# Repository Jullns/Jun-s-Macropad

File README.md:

# Macropad ✨
This is my macropad for music design and art. Following the tutorial from the blueprint program but adding some changes.

-----
## BOM:
- Seeed XIAO RP2040
- EC11 Rotary encoder
- MX-Style switches (x8)
- Blank DSA keycaps (x8)
- SK6812 MINI-E LEDs (x2)
- 4x M3x16 Bolt
- 4x M3 Heatset

## Screenshots:
- Schematic:

- PCB:

- Case:

## Challenges:

In this project, I learned a lot about using KiCad and Fusion, finally bringing the Macropad project to life. My biggest challenge was Fusion, as I had never used 3D design software before. I had to follow many steps to create the case; however, by following tutorials and doing research, I successfully completed the project and gained a great deal of knowledge.

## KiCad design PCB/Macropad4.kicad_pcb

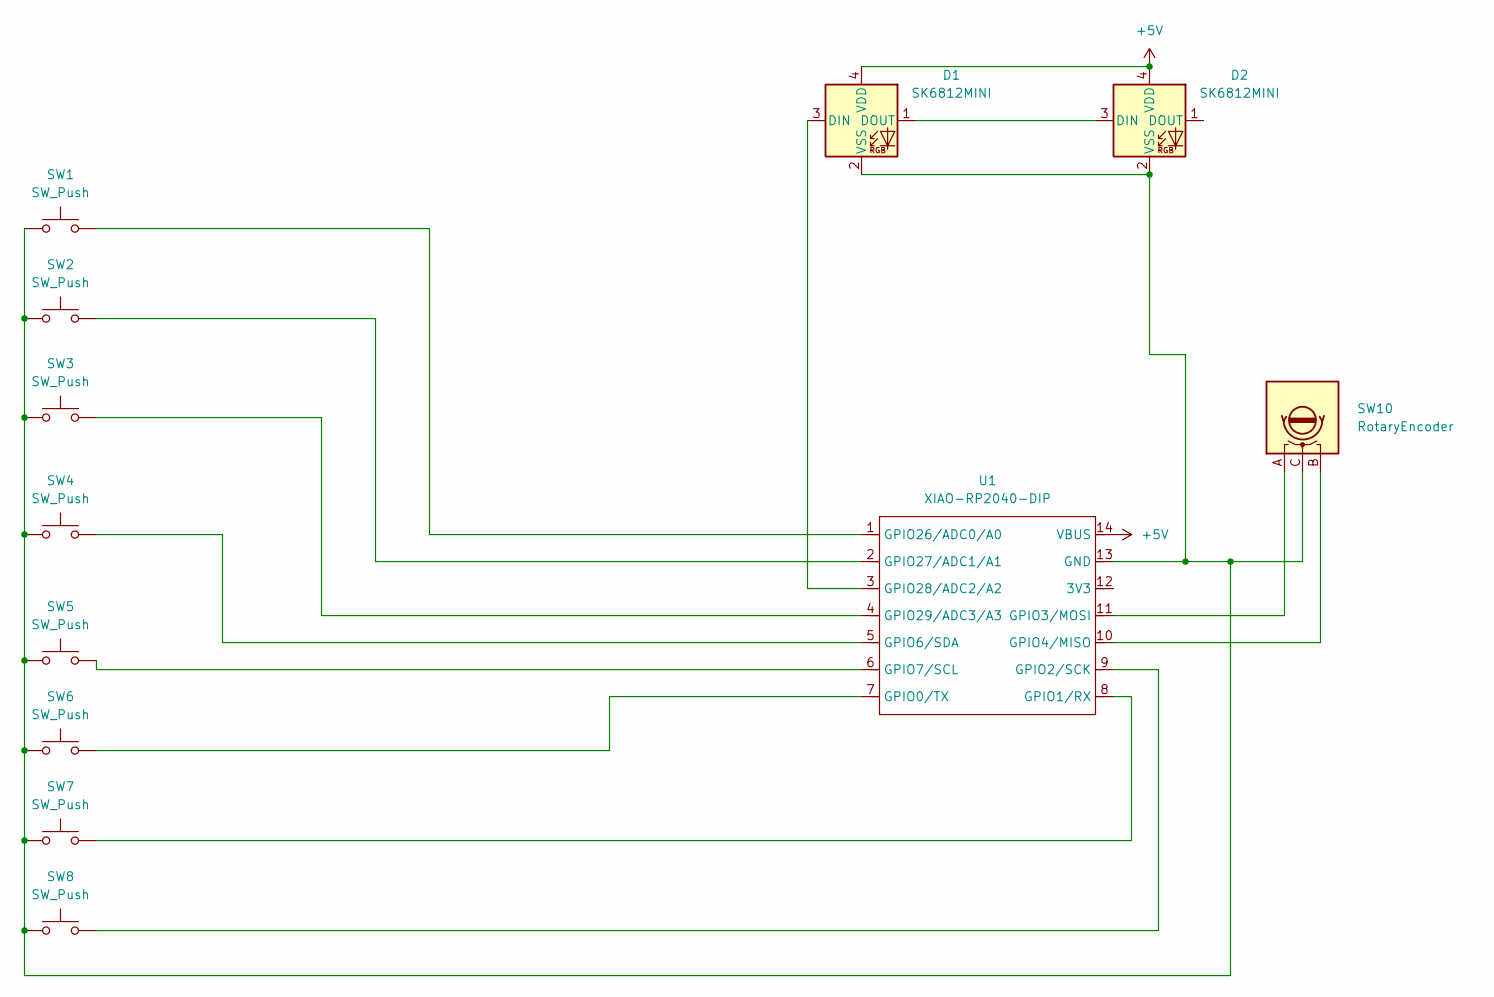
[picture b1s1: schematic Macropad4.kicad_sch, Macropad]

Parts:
D1, D2: SK6812MINI; LED_SK6812MINI_PLCC4_3.5x3.5mm_P1.75mm
SW1, SW2, SW3, SW4, SW5, SW6, SW7, SW8: SW_Push; SW_Cherry_MX_1.00u_PCB
SW10: RotaryEncoder; RotaryEncoder_Alps_EC11E_Vertical_H20mm
U1: XIAO-RP2040-DIP

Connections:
+5V: D1.4 (VDD), D2.4 (VDD), U1.14 (VBUS)
unnamed: D1.3 (DIN), U1.3 (GPIO28/ADC2/A2)
unnamed: D1.1 (DOUT), D2.3 (DIN)
unnamed: D1.2 (VSS), D2.2 (VSS), SW1.1, SW2.1, SW3.1, SW4.1, SW5.1, SW6.1, SW7.1, SW8.1, SW10.C, U1.13 (GND)
unnamed: SW6.2, U1.7 (GPIO0/TX)
unnamed: SW7.2, U1.8 (GPIO1/RX)
unnamed: SW8.2, U1.9 (GPIO2/SCK)
unnamed: SW10.A, U1.11 (GPIO3/MOSI)
unnamed: SW10.B, U1.10 (GPIO4/MISO)
unnamed: SW4.2, U1.5 (GPIO6/SDA)
unnamed: SW5.2, U1.6 (GPIO7/SCL)
unnamed: SW1.2, U1.1 (GPIO26/ADC0/A0)
unnamed: SW2.2, U1.2 (GPIO27/ADC1/A1)
unnamed: SW3.2, U1.4 (GPIO29/ADC3/A3)

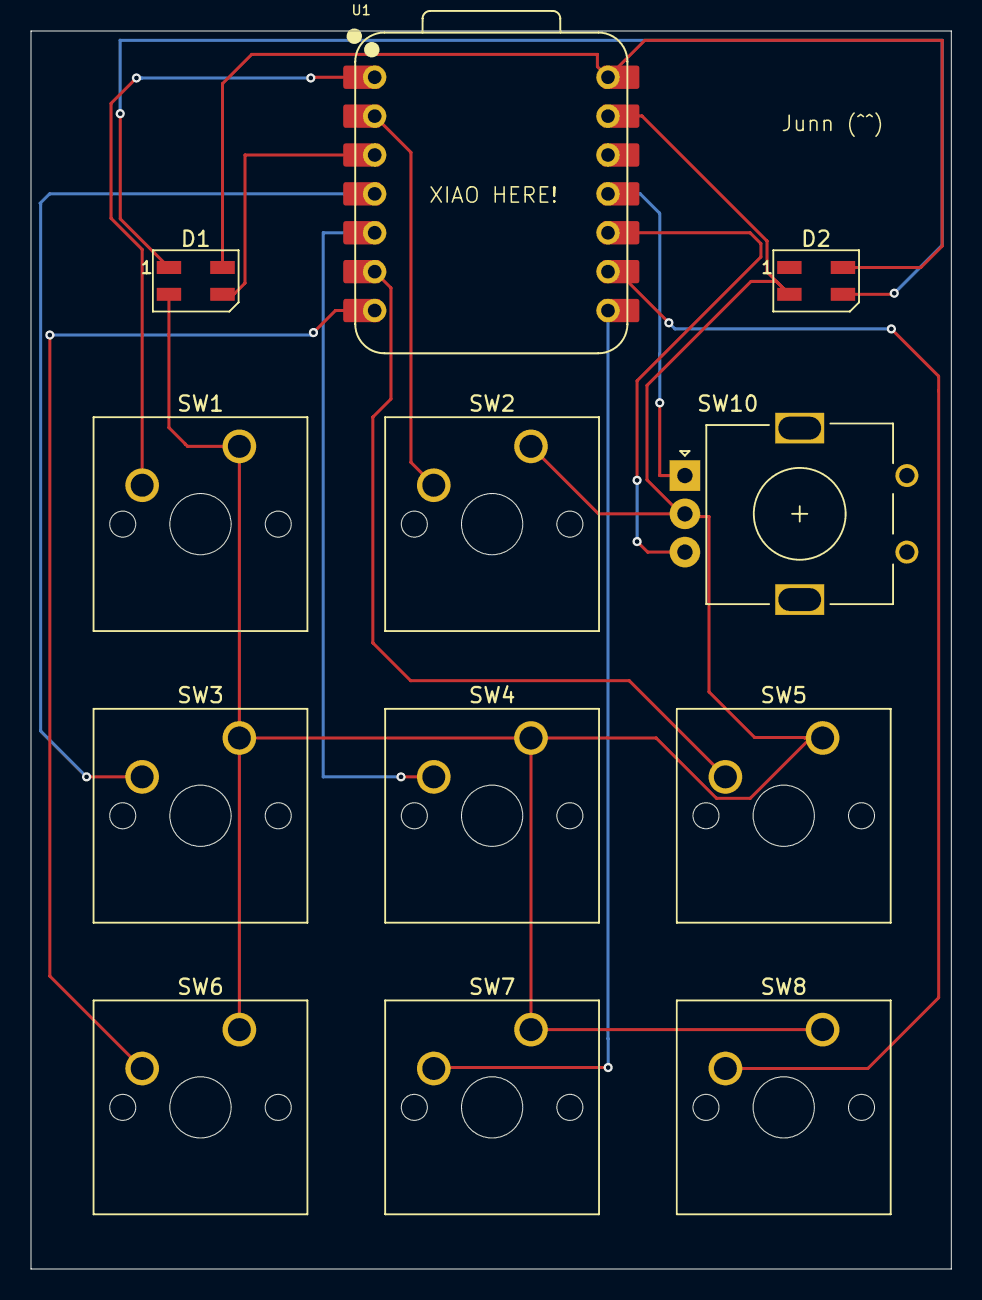
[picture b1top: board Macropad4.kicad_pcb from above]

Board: 2 copper layers, 60.1 x 80.9 mm, 12 parts (0 on the bottom side), 14 nets.

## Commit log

2025-12-27 Create s
